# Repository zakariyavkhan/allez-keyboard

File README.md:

An STM32F103 based 40% mechanical keyboard. PCB and switch plate designed in KiCAD.

- Custom firmware supported through QMK
    - [allez](https://github.com/zakariyavkhan/qmk_firmware/tree/master/keyboards/allez)
    - [allez-hw](https://github.com/zakariyavkhan/qmk_firmware/tree/master/keyboards/allez_hw)

PCBs and switch plates can be ordered through JLCPCB, who will also do PCBA for a very reasonable price. BOM will have to be generated via LCSC.

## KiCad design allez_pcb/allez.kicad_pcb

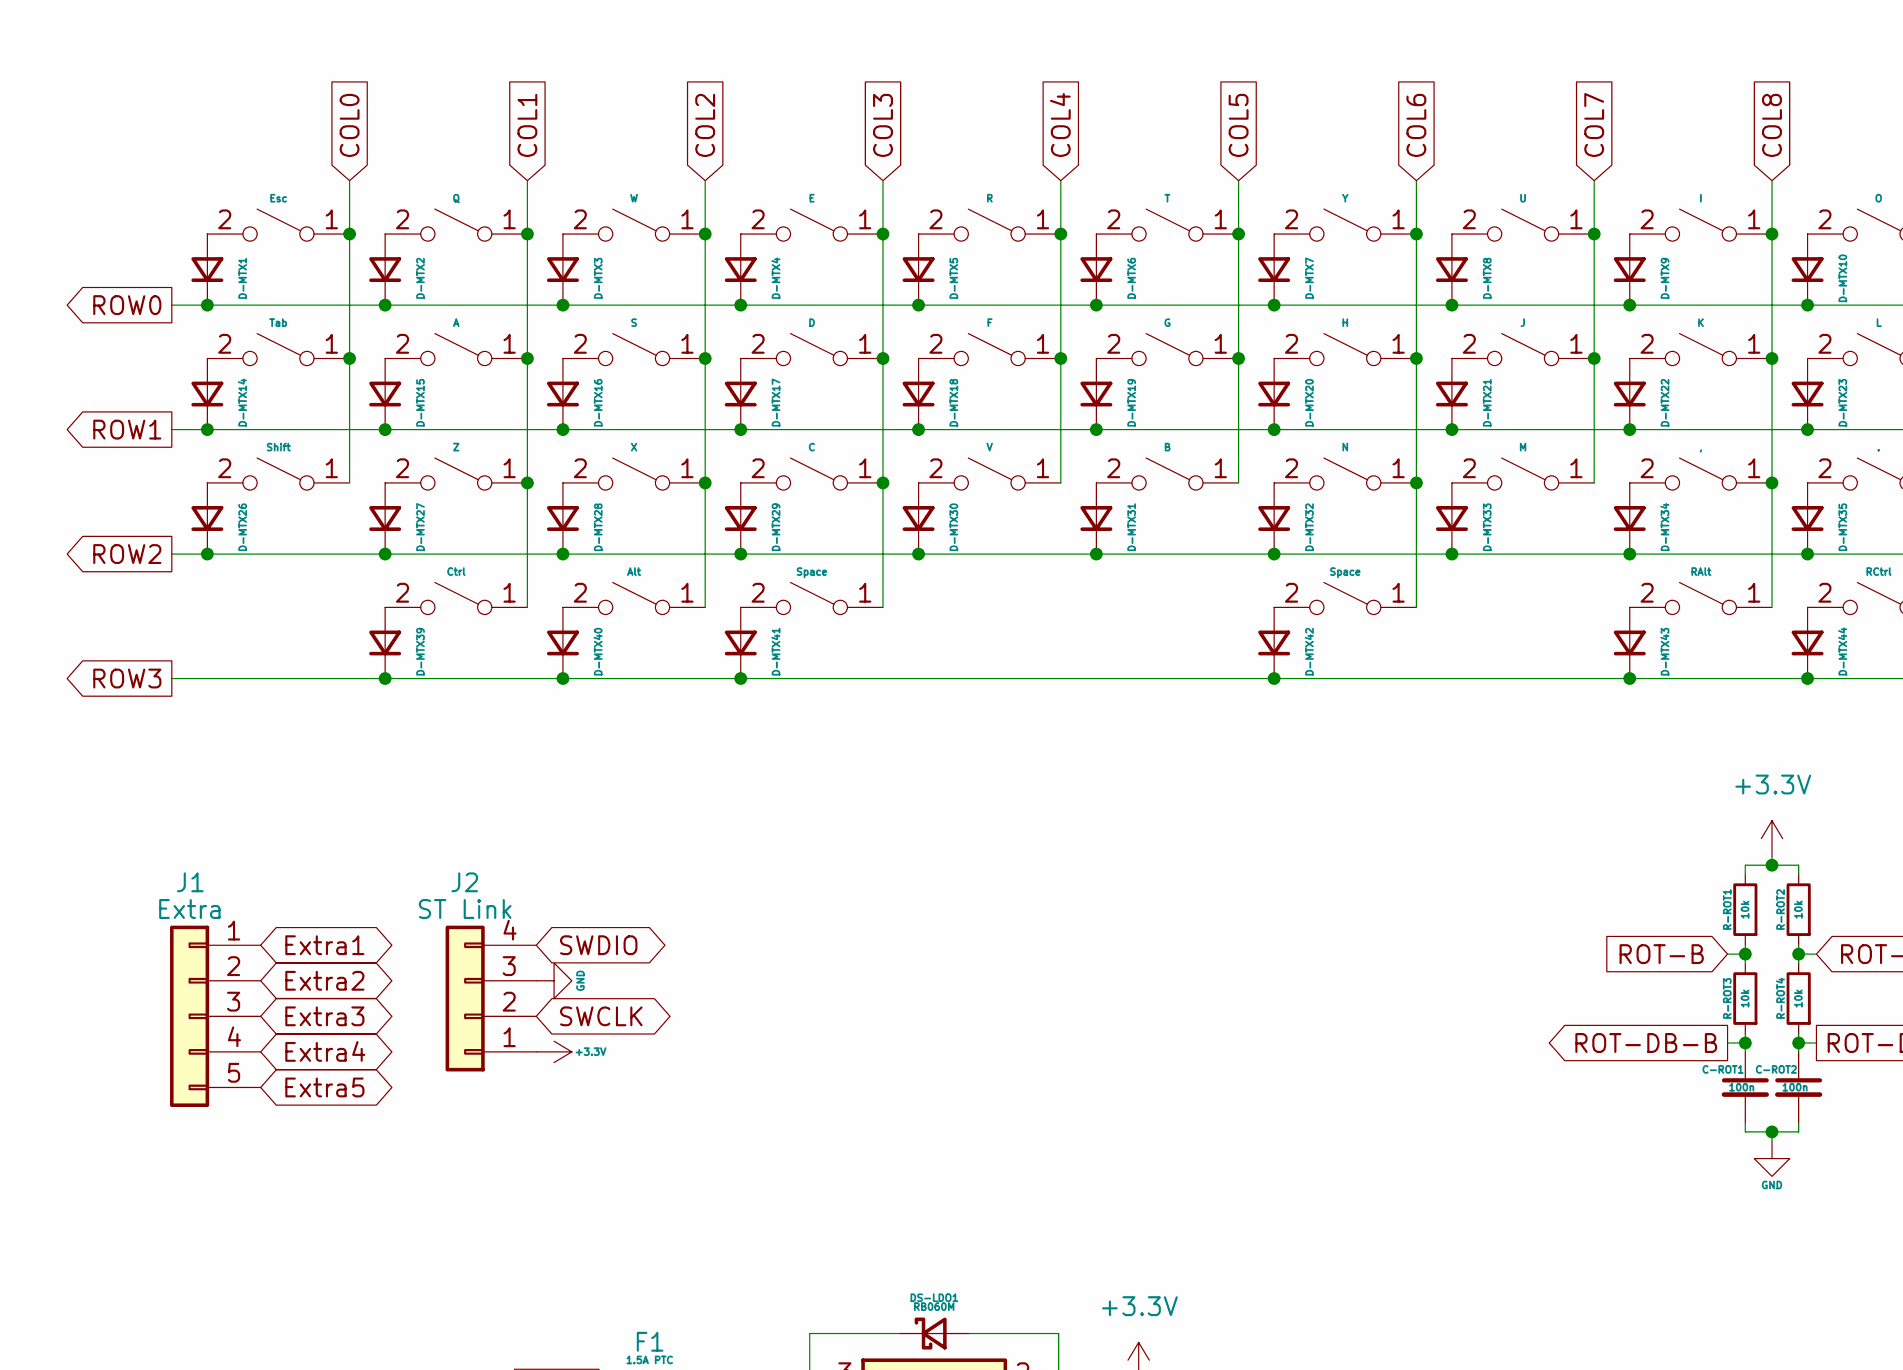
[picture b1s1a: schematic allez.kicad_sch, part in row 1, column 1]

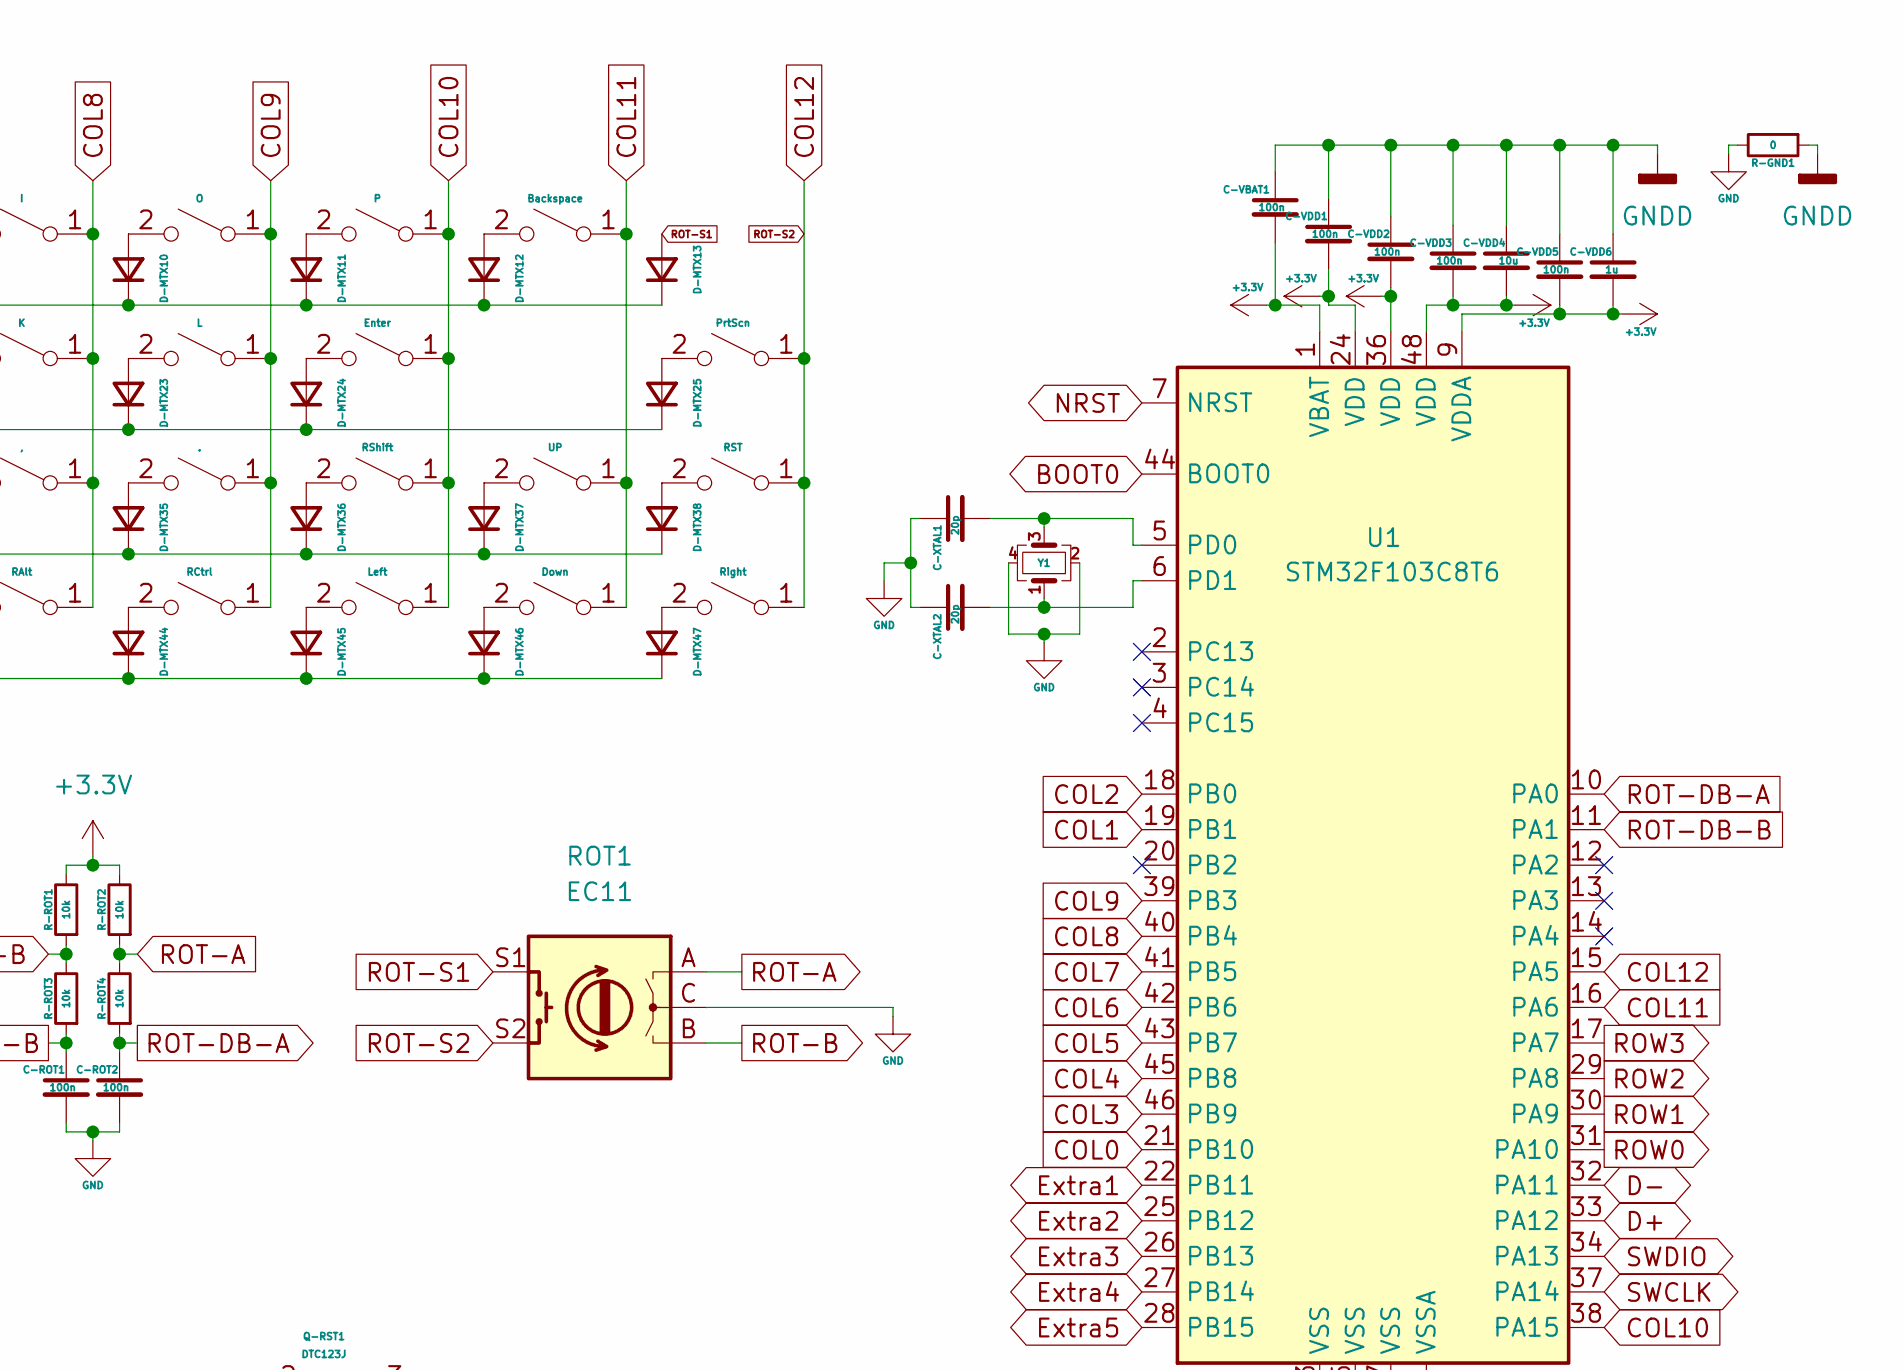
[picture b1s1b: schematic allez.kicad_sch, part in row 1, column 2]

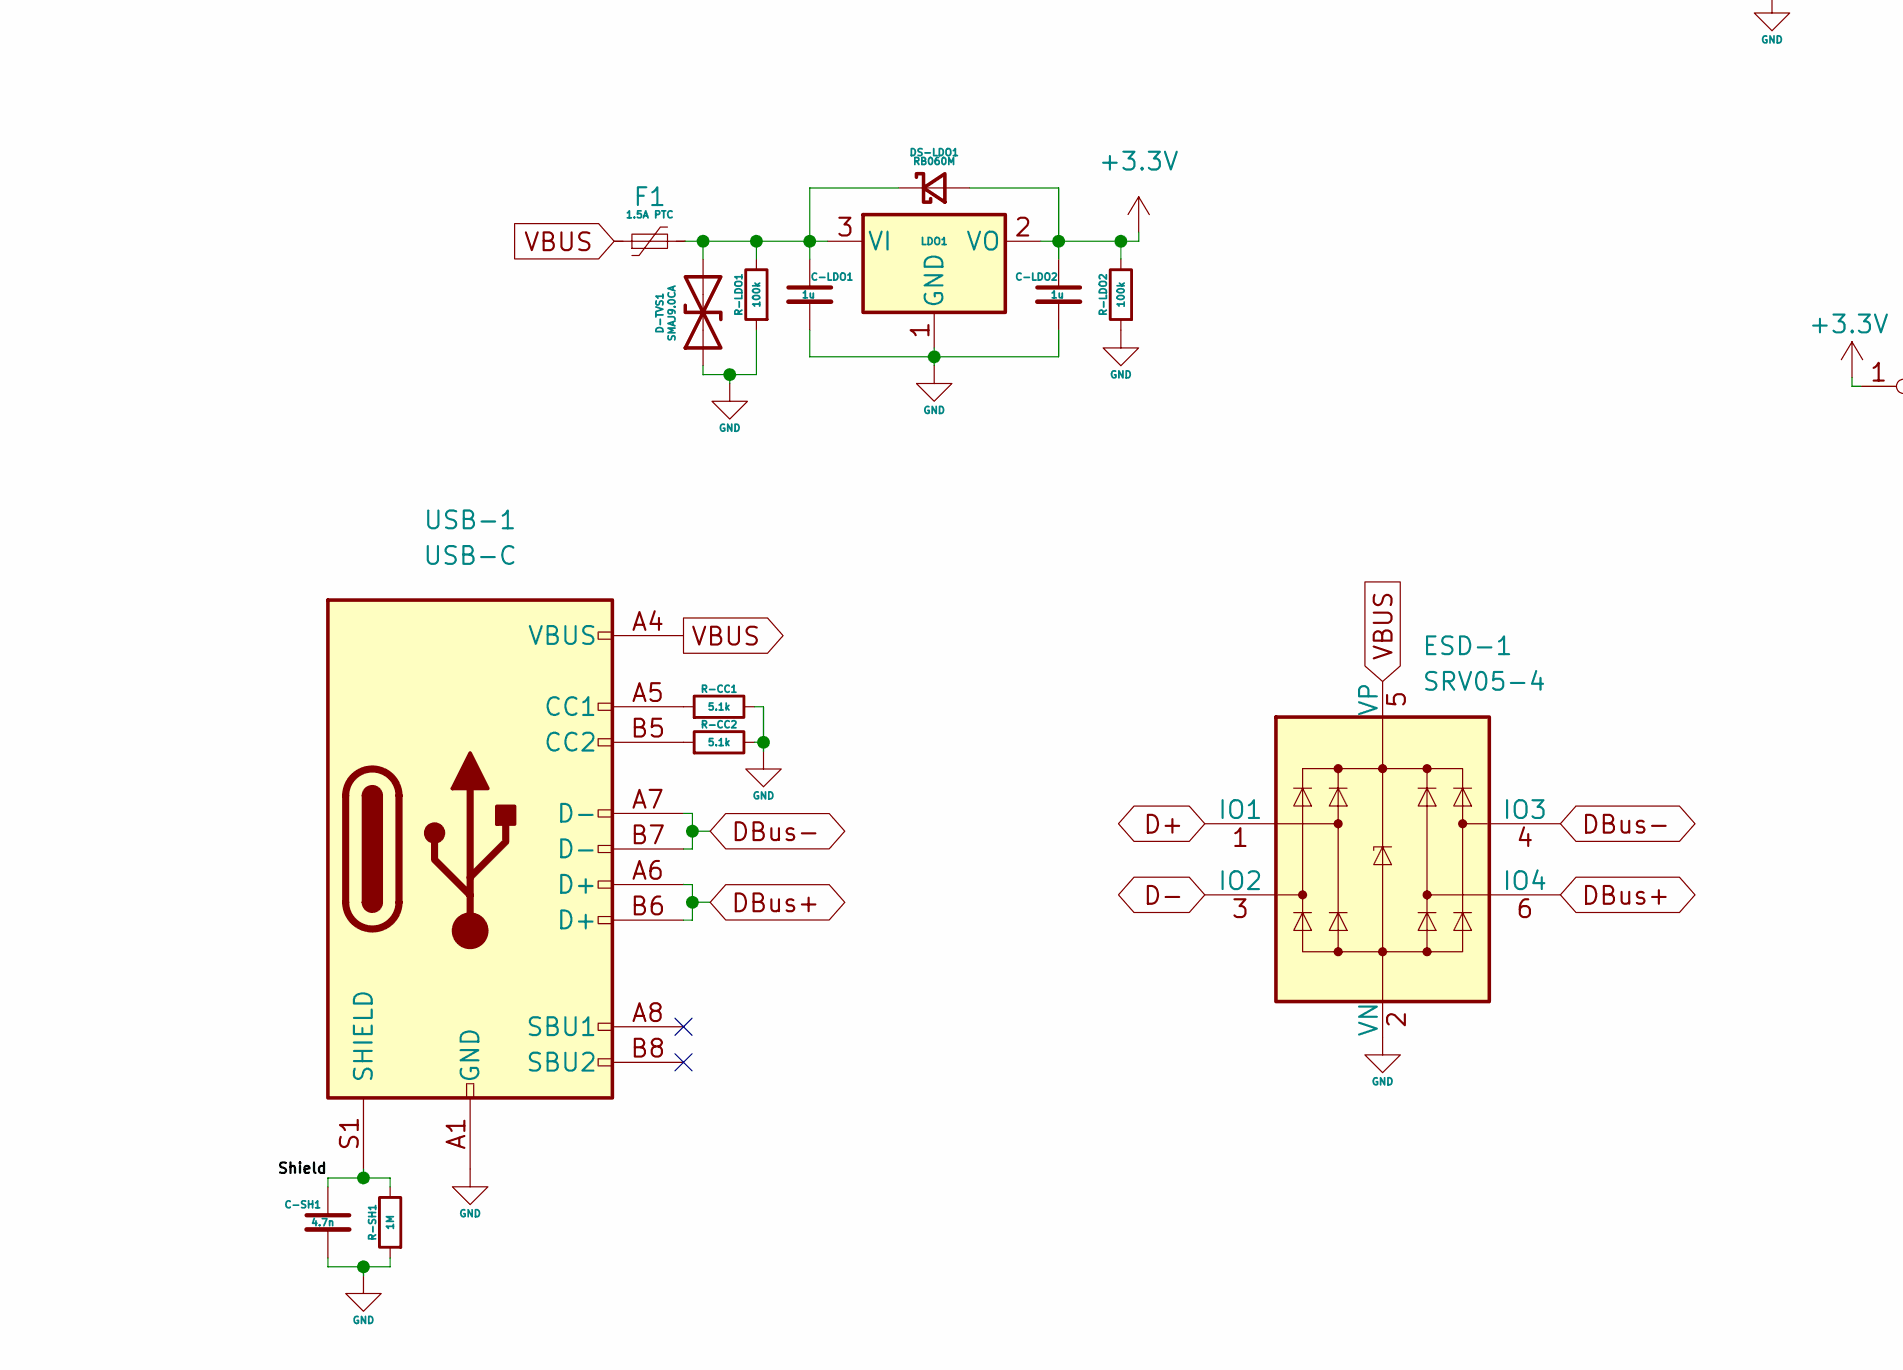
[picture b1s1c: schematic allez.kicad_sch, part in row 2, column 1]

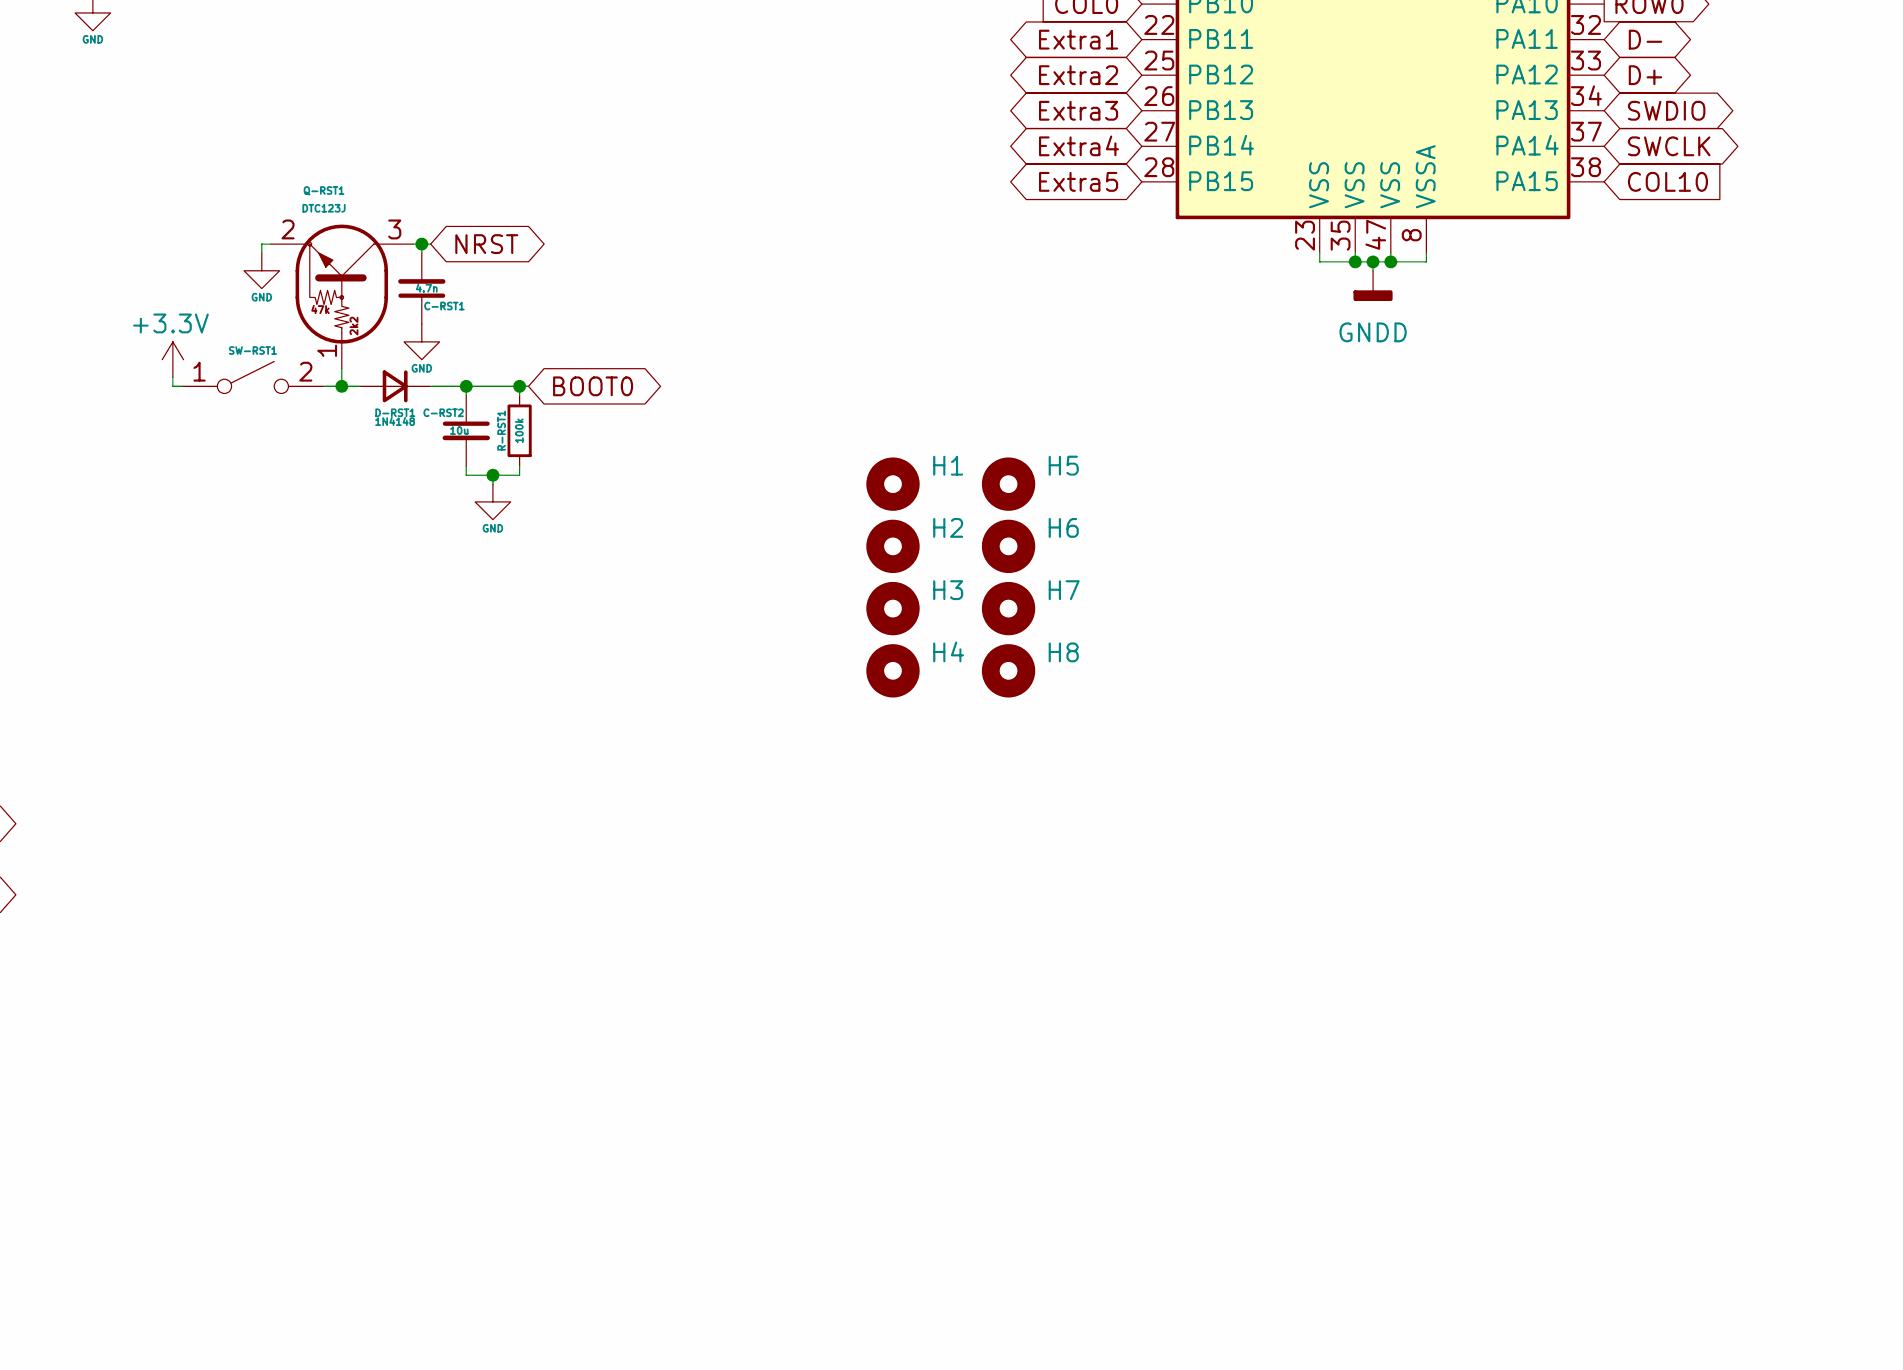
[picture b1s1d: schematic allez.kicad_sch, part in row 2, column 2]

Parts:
C-LDO1, C-LDO2: 1u; C_0603_1608Metric_Pad1.08x0.95mm_HandSolder
C-ROT1, C-ROT2: 100n; C_0603_1608Metric_Pad1.08x0.95mm_HandSolder
C-RST1: 4.7n; C_0603_1608Metric_Pad1.08x0.95mm_HandSolder
C-RST2: 10u; C_0603_1608Metric_Pad1.08x0.95mm_HandSolder
C-SH1: 4.7n; C_0603_1608Metric_Pad1.08x0.95mm_HandSolder
C-VBAT1: 100n; C_0603_1608Metric_Pad1.08x0.95mm_HandSolder
C-VDD1, C-VDD2, C-VDD3, C-VDD5: 100n; C_0603_1608Metric_Pad1.08x0.95mm_HandSolder
C-VDD4: 10u; C_0603_1608Metric_Pad1.08x0.95mm_HandSolder
C-VDD6: 1u; C_0603_1608Metric_Pad1.08x0.95mm_HandSolder
C-XTAL1, C-XTAL2: 20p; C_0603_1608Metric_Pad1.08x0.95mm_HandSolder
D-MTX1, D-MTX2, D-MTX3, D-MTX4, D-MTX5, D-MTX6, D-MTX7, D-MTX8, D-MTX9, D-MTX10, D-MTX11, D-MTX12, D-MTX13, D-MTX14, D-MTX15, D-MTX16, D-MTX17, D-MTX18, D-MTX19, D-MTX20, D-MTX21, D-MTX22, D-MTX23, D-MTX24, D-MTX25, D-MTX26, D-MTX27, D-MTX28, D-MTX29, D-MTX30, D-MTX31, D-MTX32, D-MTX33, D-MTX34, D-MTX35, D-MTX36, D-MTX37, D-MTX38, D-MTX39, D-MTX40, D-MTX41, D-MTX42, D-MTX43, D-MTX44, D-MTX45, D-MTX46, D-MTX47: 1N4148; D_0603_1608Metric_Pad1.05x0.95mm_HandSolder
D-RST1: 1N4148; D_0603_1608Metric_Pad1.05x0.95mm_HandSolder
D-TVS1: SMAJ9.0CA; D_SMA
DS-LDO1: RB060M; D_SOD-123F
ESD-1: SRV05-4; SOT-23-6
F1: 1.5A PTC; Fuse_1812_4532Metric_Pad1.30x3.40mm_HandSolder
H1, H2, H3, H4, H5, H6, H7, H8: MountingHole; MountingHole_3.2mm_M3
J1: Extra; PinHeader_1x05_P2.54mm_Vertical
J2: ST Link; PinHeader_1x04_P2.54mm_Vertical
LDO1: XC6206; SOT-23
MX1: Esc; SW_Cherry_MX_1.00u_PCB
MX2: Q; SW_Cherry_MX_1.00u_PCB
MX3: W; SW_Cherry_MX_1.00u_PCB
MX4: E; SW_Cherry_MX_1.00u_PCB
MX5: R; SW_Cherry_MX_1.00u_PCB
MX6: T; SW_Cherry_MX_1.00u_PCB
MX7: Y; SW_Cherry_MX_1.00u_PCB
MX8: U; SW_Cherry_MX_1.00u_PCB
MX9: I; SW_Cherry_MX_1.00u_PCB
MX10: O; SW_Cherry_MX_1.00u_PCB
MX11: P; SW_Cherry_MX_1.00u_PCB
MX12: Backspace; SW_Cherry_MX_1.00u_PCB
MX14: Tab; SW_Cherry_MX_1.25u_PCB
MX15: A; SW_Cherry_MX_1.00u_PCB
MX16: S; SW_Cherry_MX_1.00u_PCB
MX17: D; SW_Cherry_MX_1.00u_PCB
MX18: F; SW_Cherry_MX_1.00u_PCB
MX19: G; SW_Cherry_MX_1.00u_PCB
MX20: H; SW_Cherry_MX_1.00u_PCB
MX21: J; SW_Cherry_MX_1.00u_PCB
MX22: K; SW_Cherry_MX_1.00u_PCB
MX23: L; SW_Cherry_MX_1.00u_PCB
MX24: Enter; SW_Cherry_MX_1.75u_PCB
MX25: PrtScn; SW_Cherry_MX_1.00u_PCB
MX26: Shift; SW_Cherry_MX_1.50u_PCB
MX27: Z; SW_Cherry_MX_1.00u_PCB
MX28: X; SW_Cherry_MX_1.00u_PCB
MX29: C; SW_Cherry_MX_1.00u_PCB
MX30: V; SW_Cherry_MX_1.00u_PCB
MX31: B; SW_Cherry_MX_1.00u_PCB
MX32: N; SW_Cherry_MX_1.00u_PCB
MX33: M; SW_Cherry_MX_1.00u_PCB
MX34: ,; SW_Cherry_MX_1.00u_PCB
MX35: .; SW_Cherry_MX_1.00u_PCB
MX36: RShift; SW_Cherry_MX_1.25u_PCB
MX37: UP; SW_Cherry_MX_1.00u_PCB
MX38: RST; SW_Cherry_MX_1.00u_PCB
MX39: Ctrl; SW_Cherry_MX_1.25u_PCB
MX40: Alt; SW_Cherry_MX_1.00u_PCB
MX41: Space; SW_Cherry_MX_2.25u_PCB
MX42: Space; SW_Cherry_MX_2.75u_PCB
MX43: RAlt; SW_Cherry_MX_1.00u_PCB
MX44: RCtrl; SW_Cherry_MX_1.25u_PCB
MX45: Left; SW_Cherry_MX_1.00u_PCB
MX46: Down; SW_Cherry_MX_1.00u_PCB
MX47: Right; SW_Cherry_MX_1.00u_PCB
Q-RST1: DTC123J; SOT-23
R-CC1, R-CC2: 5.1k; R_0603_1608Metric_Pad0.98x0.95mm_HandSolder
R-GND1: 0; R_0603_1608Metric_Pad0.98x0.95mm_HandSolder
R-LDO1, R-LDO2: 100k; R_0603_1608Metric_Pad0.98x0.95mm_HandSolder
R-ROT1, R-ROT2, R-ROT3, R-ROT4: 10k; R_0603_1608Metric_Pad0.98x0.95mm_HandSolder
R-RST1: 100k; R_0603_1608Metric_Pad0.98x0.95mm_HandSolder
R-SH1: 1M; R_0603_1608Metric_Pad0.98x0.95mm_HandSolder
ROT1: EC11; RotaryEncoder_Alps_EC11E-Switch_Vertical_H20mm
SW-RST1: SPST; SW_SPST_TL3342
U1: STM32F103C8T6; LQFP-48_7x7mm_P0.5mm
USB-1: USB-C; USB_C_Receptacle_HRO_TYPE-C-31-M-12
Y1: 8MHz; Crystal_SMD_3225-4Pin_3.2x2.5mm_HandSoldering

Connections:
+3.3V: C-LDO2.1, C-VBAT1.2, C-VDD1.2, C-VDD2.2, C-VDD3.2, C-VDD4.2, C-VDD5.2, C-VDD6.2, DS-LDO1.2 (A), J2.1, LDO1.2 (VO), R-LDO2.2, R-ROT1.2, R-ROT2.2, SW-RST1.1 (A), U1.1 (VBAT), U1.9 (VDDA), U1.24 (VDD), U1.36 (VDD), U1.48 (VDD)
/Shield: C-SH1.1, R-SH1.2, USB-1.S1 (SHIELD)
BOOT0: C-RST2.1, D-RST1.1 (K), R-RST1.2, U1.44 (BOOT0)
COL0: MX1.1 (A), MX14.1 (A), MX26.1 (A), U1.21 (PB10)
COL1: MX2.1 (A), MX15.1 (A), MX27.1 (A), MX39.1 (A), U1.19 (PB1)
COL2: MX3.1 (A), MX16.1 (A), MX28.1 (A), MX40.1 (A), U1.18 (PB0)
COL3: MX4.1 (A), MX17.1 (A), MX29.1 (A), MX41.1 (A), U1.46 (PB9)
COL4: MX5.1 (A), MX18.1 (A), MX30.1 (A), U1.45 (PB8)
COL5: MX6.1 (A), MX19.1 (A), MX31.1 (A), U1.43 (PB7)
COL6: MX7.1 (A), MX20.1 (A), MX32.1 (A), MX42.1 (A), U1.42 (PB6)
COL7: MX8.1 (A), MX21.1 (A), MX33.1 (A), U1.41 (PB5)
COL8: MX9.1 (A), MX22.1 (A), MX34.1 (A), MX43.1 (A), U1.40 (PB4)
COL9: MX10.1 (A), MX23.1 (A), MX35.1 (A), MX44.1 (A), U1.39 (PB3)
COL10: MX11.1 (A), MX24.1 (A), MX36.1 (A), MX45.1 (A), U1.38 (PA15)
COL11: MX12.1 (A), MX37.1 (A), MX46.1 (A), U1.16 (PA6)
COL12: MX25.1 (A), MX38.1 (A), MX47.1 (A), ROT1.S2, U1.15 (PA5)
D+: ESD-1.1 (IO1), U1.33 (PA12)
D-: ESD-1.3 (IO2), U1.32 (PA11)
DBus+: ESD-1.6 (IO4), USB-1.A6 (D+), USB-1.B6 (D+)
DBus-: ESD-1.4 (IO3), USB-1.A7 (D-), USB-1.B7 (D-)
Extra1: J1.1, U1.22 (PB11)
Extra2: J1.2, U1.25 (PB12)
Extra3: J1.3, U1.26 (PB13)
Extra4: J1.4, U1.27 (PB14)
Extra5: J1.5, U1.28 (PB15)
GND: C-LDO1.2, C-LDO2.2, C-ROT1.2, C-ROT2.2, C-RST1.1, C-RST2.2, C-SH1.2, C-XTAL1.1, C-XTAL2.1, D-TVS1.1 (A1), ESD-1.2 (VN), J2.3, LDO1.1 (GND), Q-RST1.2 (E), R-CC1.2, R-CC2.2, R-GND1.2, R-LDO1.1, R-LDO2.1, R-RST1.1, R-SH1.1, ROT1.C, USB-1.A1 (GND), USB-1.A12 (GND), USB-1.B1 (GND), USB-1.B12 (GND), Y1.2, Y1.4
GNDD: C-VBAT1.1, C-VDD1.1, C-VDD2.1, C-VDD3.1, C-VDD4.1, C-VDD5.1, C-VDD6.1, R-GND1.1, U1.8 (VSSA), U1.23 (VSS), U1.35 (VSS), U1.47 (VSS)
NRST: C-RST1.2, Q-RST1.3 (C), U1.7 (NRST)
unnamed: C-LDO1.1, D-TVS1.2 (A2), DS-LDO1.1 (K), F1.2, LDO1.3 (VI), R-LDO1.2
unnamed: C-XTAL1.2, U1.5 (PD0), Y1.3
unnamed: C-XTAL2.2, U1.6 (PD1), Y1.1
unnamed: D-MTX1.2 (A), MX1.2 (B)
unnamed: D-MTX2.2 (A), MX2.2 (B)
unnamed: D-MTX3.2 (A), MX3.2 (B)
unnamed: D-MTX4.2 (A), MX4.2 (B)
unnamed: D-MTX5.2 (A), MX5.2 (B)
unnamed: D-MTX6.2 (A), MX6.2 (B)
unnamed: D-MTX7.2 (A), MX7.2 (B)
unnamed: D-MTX8.2 (A), MX8.2 (B)
unnamed: D-MTX9.2 (A), MX9.2 (B)
unnamed: D-MTX10.2 (A), MX10.2 (B)
unnamed: D-MTX11.2 (A), MX11.2 (B)
unnamed: D-MTX12.2 (A), MX12.2 (B)
unnamed: D-MTX14.2 (A), MX14.2 (B)
unnamed: D-MTX15.2 (A), MX15.2 (B)
unnamed: D-MTX16.2 (A), MX16.2 (B)
unnamed: D-MTX17.2 (A), MX17.2 (B)
unnamed: D-MTX18.2 (A), MX18.2 (B)
unnamed: D-MTX19.2 (A), MX19.2 (B)
unnamed: D-MTX20.2 (A), MX20.2 (B)
unnamed: D-MTX21.2 (A), MX21.2 (B)
unnamed: D-MTX22.2 (A), MX22.2 (B)
unnamed: D-MTX23.2 (A), MX23.2 (B)
unnamed: D-MTX24.2 (A), MX24.2 (B)
unnamed: D-MTX25.2 (A), MX25.2 (B)
unnamed: D-MTX26.2 (A), MX26.2 (B)
unnamed: D-MTX27.2 (A), MX27.2 (B)
unnamed: D-MTX28.2 (A), MX28.2 (B)
unnamed: D-MTX29.2 (A), MX29.2 (B)
unnamed: D-MTX30.2 (A), MX30.2 (B)
unnamed: D-MTX31.2 (A), MX31.2 (B)
unnamed: D-MTX32.2 (A), MX32.2 (B)
unnamed: D-MTX33.2 (A), MX33.2 (B)
unnamed: D-MTX34.2 (A), MX34.2 (B)
unnamed: D-MTX35.2 (A), MX35.2 (B)
unnamed: D-MTX36.2 (A), MX36.2 (B)
unnamed: D-MTX37.2 (A), MX37.2 (B)
unnamed: D-MTX38.2 (A), MX38.2 (B)
unnamed: D-MTX39.2 (A), MX39.2 (B)
unnamed: D-MTX40.2 (A), MX40.2 (B)
unnamed: D-MTX41.2 (A), MX41.2 (B)
unnamed: D-MTX42.2 (A), MX42.2 (B)
unnamed: D-MTX43.2 (A), MX43.2 (B)
unnamed: D-MTX44.2 (A), MX44.2 (B)
unnamed: D-MTX45.2 (A), MX45.2 (B)
unnamed: D-MTX46.2 (A), MX46.2 (B)
unnamed: D-MTX47.2 (A), MX47.2 (B)
unnamed: D-RST1.2 (A), Q-RST1.1 (B), SW-RST1.2 (B)
unnamed: R-CC1.1, USB-1.A5 (CC1)
unnamed: R-CC2.1, USB-1.B5 (CC2)
ROT-A: R-ROT2.1, R-ROT4.2, ROT1.A
ROT-B: R-ROT1.1, R-ROT3.2, ROT1.B
ROT-DB-A: C-ROT2.1, R-ROT4.1, U1.10 (PA0)
ROT-DB-B: C-ROT1.1, R-ROT3.1, U1.11 (PA1)
ROT-S1: D-MTX13.2 (A), ROT1.S1
ROW0: D-MTX1.1 (K), D-MTX2.1 (K), D-MTX3.1 (K), D-MTX4.1 (K), D-MTX5.1 (K), D-MTX6.1 (K), D-MTX7.1 (K), D-MTX8.1 (K), D-MTX9.1 (K), D-MTX10.1 (K), D-MTX11.1 (K), D-MTX12.1 (K), D-MTX13.1 (K), U1.31 (PA10)
ROW1: D-MTX14.1 (K), D-MTX15.1 (K), D-MTX16.1 (K), D-MTX17.1 (K), D-MTX18.1 (K), D-MTX19.1 (K), D-MTX20.1 (K), D-MTX21.1 (K), D-MTX22.1 (K), D-MTX23.1 (K), D-MTX24.1 (K), D-MTX25.1 (K), U1.30 (PA9)
ROW2: D-MTX26.1 (K), D-MTX27.1 (K), D-MTX28.1 (K), D-MTX29.1 (K), D-MTX30.1 (K), D-MTX31.1 (K), D-MTX32.1 (K), D-MTX33.1 (K), D-MTX34.1 (K), D-MTX35.1 (K), D-MTX36.1 (K), D-MTX37.1 (K), D-MTX38.1 (K), U1.29 (PA8)
ROW3: D-MTX39.1 (K), D-MTX40.1 (K), D-MTX41.1 (K), D-MTX42.1 (K), D-MTX43.1 (K), D-MTX44.1 (K), D-MTX45.1 (K), D-MTX46.1 (K), D-MTX47.1 (K), U1.17 (PA7)
SWCLK: J2.2, U1.37 (PA14)
SWDIO: J2.4, U1.34 (PA13)
VBUS: ESD-1.5 (VP), F1.1, USB-1.A4 (VBUS), USB-1.A9 (VBUS), USB-1.B4 (VBUS), USB-1.B9 (VBUS)

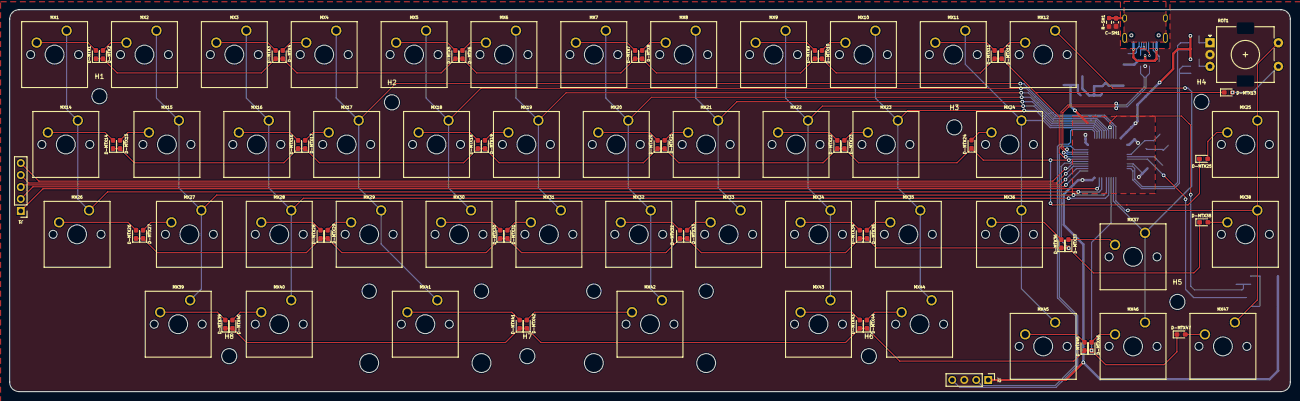
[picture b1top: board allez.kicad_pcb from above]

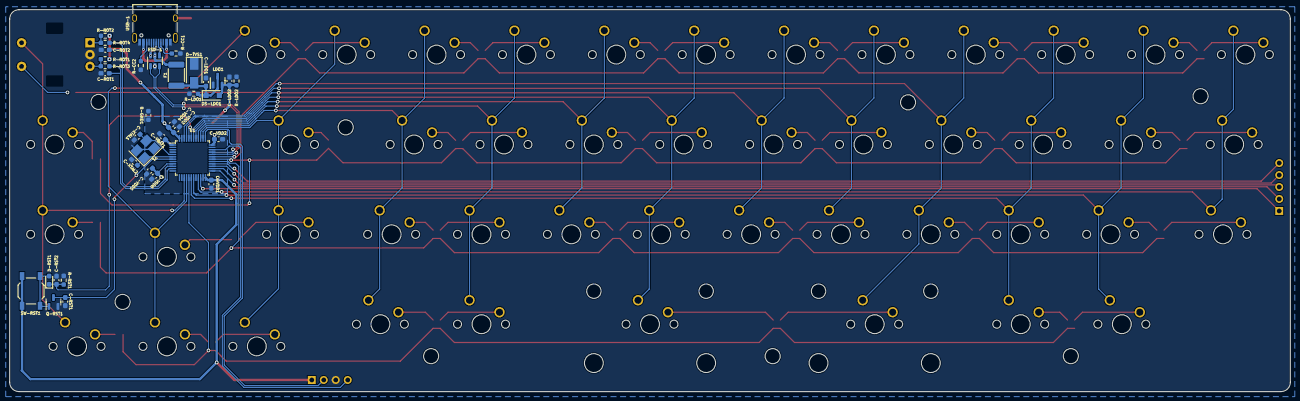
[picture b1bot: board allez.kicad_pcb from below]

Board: 2 copper layers, 271.5 x 81.0 mm, 142 parts (36 on the bottom side), 92 nets.

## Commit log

2022-10-22 add files
